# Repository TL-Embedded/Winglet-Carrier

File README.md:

# Winglet Carrier

This is a development board to faciliate testing of the [winglet modems](./winglet-modem.md).

This provides power and connectivity to the modem, and access to all interfaces.

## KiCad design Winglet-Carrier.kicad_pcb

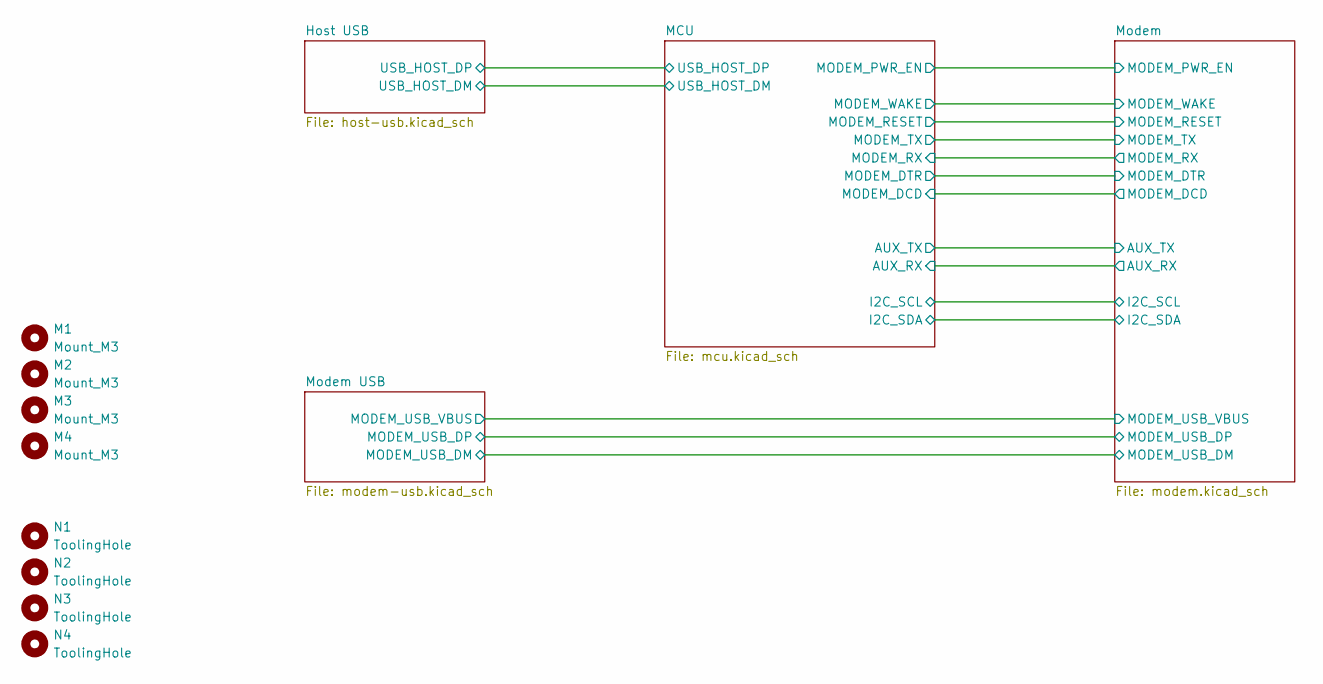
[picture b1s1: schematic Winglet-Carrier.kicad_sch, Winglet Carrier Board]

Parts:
M1, M2, M3, M4: Mount_M3
N1, N2, N3, N4: ToolingHole; ToolingHole_1mm

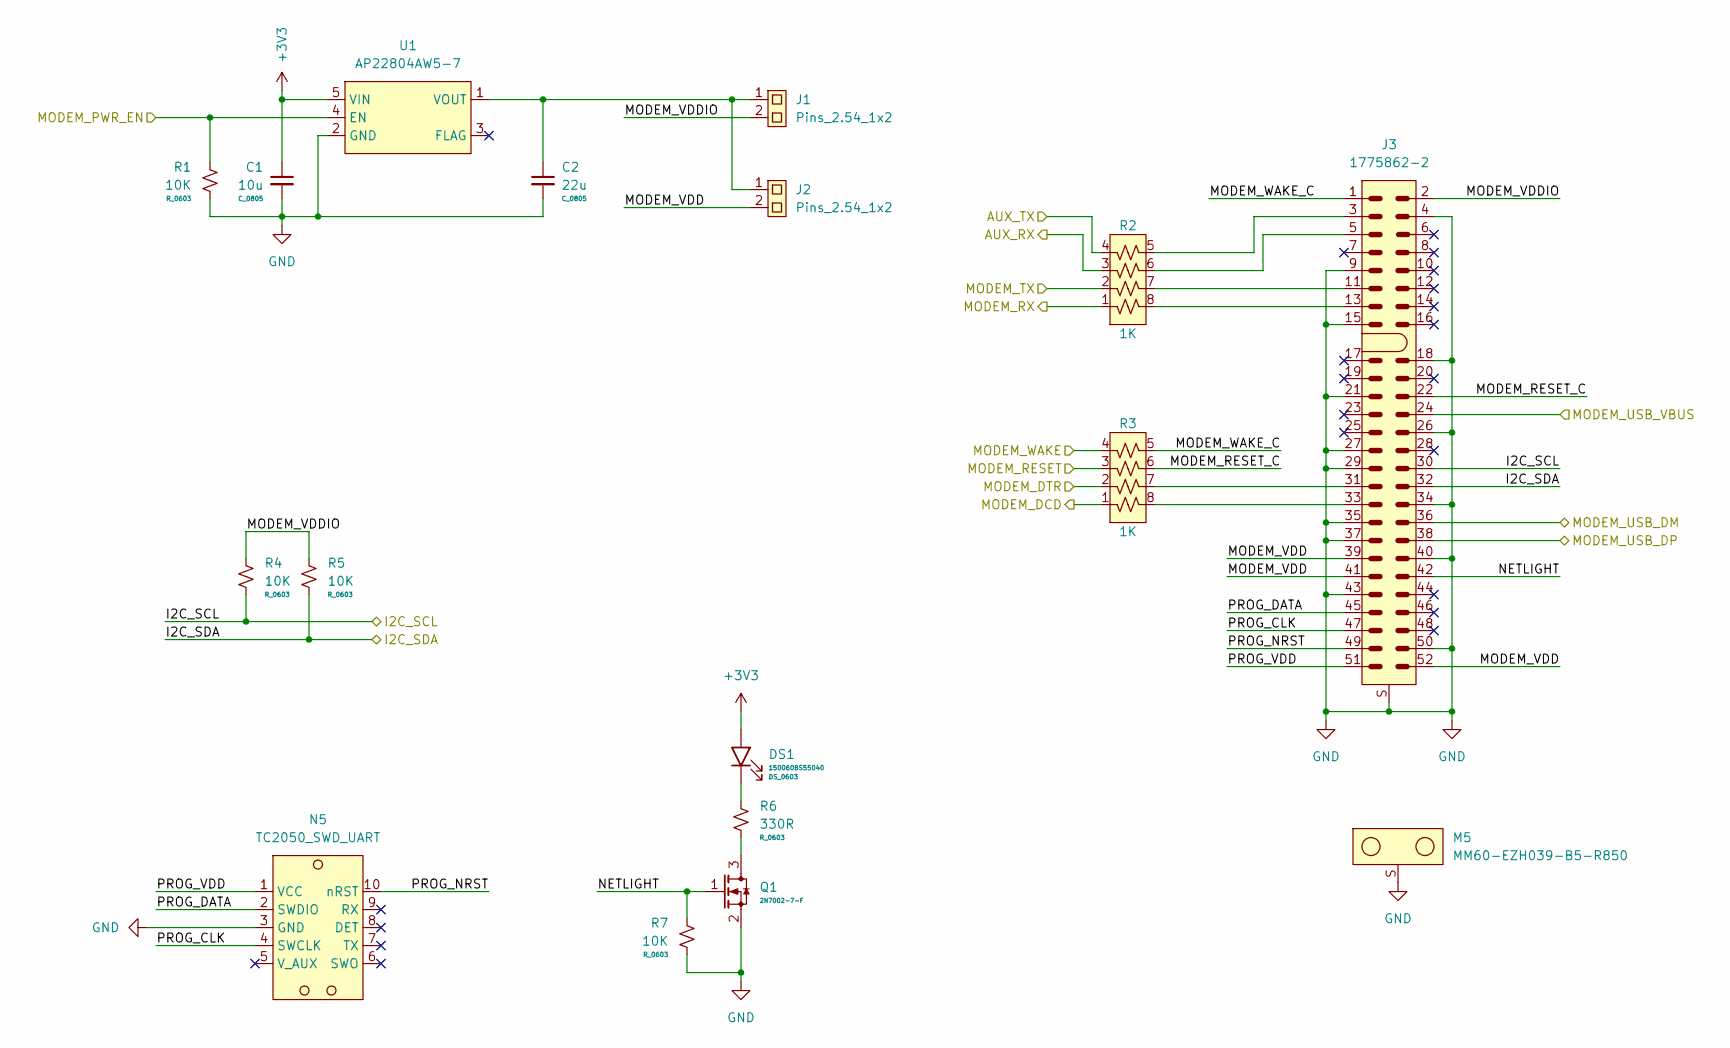
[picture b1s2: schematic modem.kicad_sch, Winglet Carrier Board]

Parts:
C1: 10u; C_0805
C2: 22u; C_0805
DS1: 150060BS55040; DS_0603
J1, J2: Pins_2.54_1x2; Pins-2.54-1x2
J3: 1775862-2
M5: MM60-EZH039-B5-R850
N5: TC2050_SWD_UART; TagConnect_TC2050
Q1: 2N7002-7-F; SOT23_3
R1, R4, R5, R7: 10K; R_0603
R2, R3: 1K; R_Array_1206
R6: 330R; R_0603
U1: AP22804AW5-7; SOT23_5

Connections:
+3V3: C1.1, DS1.2 (A), U1.5 (VIN); also elsewhere on the board
/MCU/AUX_RX: R2.3; also elsewhere on the board
/MCU/AUX_TX: R2.4; also elsewhere on the board
/MCU/MODEM_DCD: R3.1; also elsewhere on the board
/MCU/MODEM_DTR: R3.2; also elsewhere on the board
/MCU/MODEM_PWR_EN: R1.1, U1.4 (EN); also elsewhere on the board
/MCU/MODEM_RESET: R3.3; also elsewhere on the board
/MCU/MODEM_RX: R2.1; also elsewhere on the board
/MCU/MODEM_TX: R2.2; also elsewhere on the board
/MCU/MODEM_WAKE: R3.4; also elsewhere on the board
/Modem USB/MODEM_USB_DM: J3.36; also elsewhere on the board
/Modem USB/MODEM_USB_DP: J3.38; also elsewhere on the board
/Modem USB/MODEM_USB_VBUS: J3.24; also elsewhere on the board
/Modem/I2C_SCL: J3.30, R4.2; also elsewhere on the board
/Modem/I2C_SDA: J3.32, R5.2; also elsewhere on the board
/Modem/MODEM_RESET_C: J3.22, R3.6
/Modem/MODEM_VDD: J2.2, J3.39, J3.41, J3.52
/Modem/MODEM_VDDIO: J1.2, J3.2, R4.1, R5.1
/Modem/MODEM_WAKE_C: J3.1, R3.5
/Modem/NETLIGHT: J3.42, Q1.1 (G), R7.1
/Modem/PROG_CLK: J3.47, N5.4 (SWCLK)
/Modem/PROG_DATA: J3.45, N5.2 (SWDIO)
/Modem/PROG_NRST: J3.49, N5.10 (nRST)
/Modem/PROG_VDD: J3.51, N5.1 (VCC)
GND: C1.2, C2.2, J3.4, J3.9, J3.15, J3.18, J3.21, J3.26, J3.27, J3.29, J3.34, J3.35, J3.37, J3.40, J3.43, J3.50, J3.S, M5.S, N5.3 (GND), Q1.2 (S), R1.2, R7.2, U1.2 (GND); also elsewhere on the board
unnamed: DS1.1 (K), R6.1
unnamed: J3.3, R2.5
unnamed: J3.5, R2.6
unnamed: J3.11, R2.7
unnamed: J3.13, R2.8
unnamed: J3.31, R3.7
unnamed: J3.33, R3.8
unnamed: Q1.3 (D), R6.2
unnamed: C2.1, J1.1, J2.1, U1.1 (VOUT)

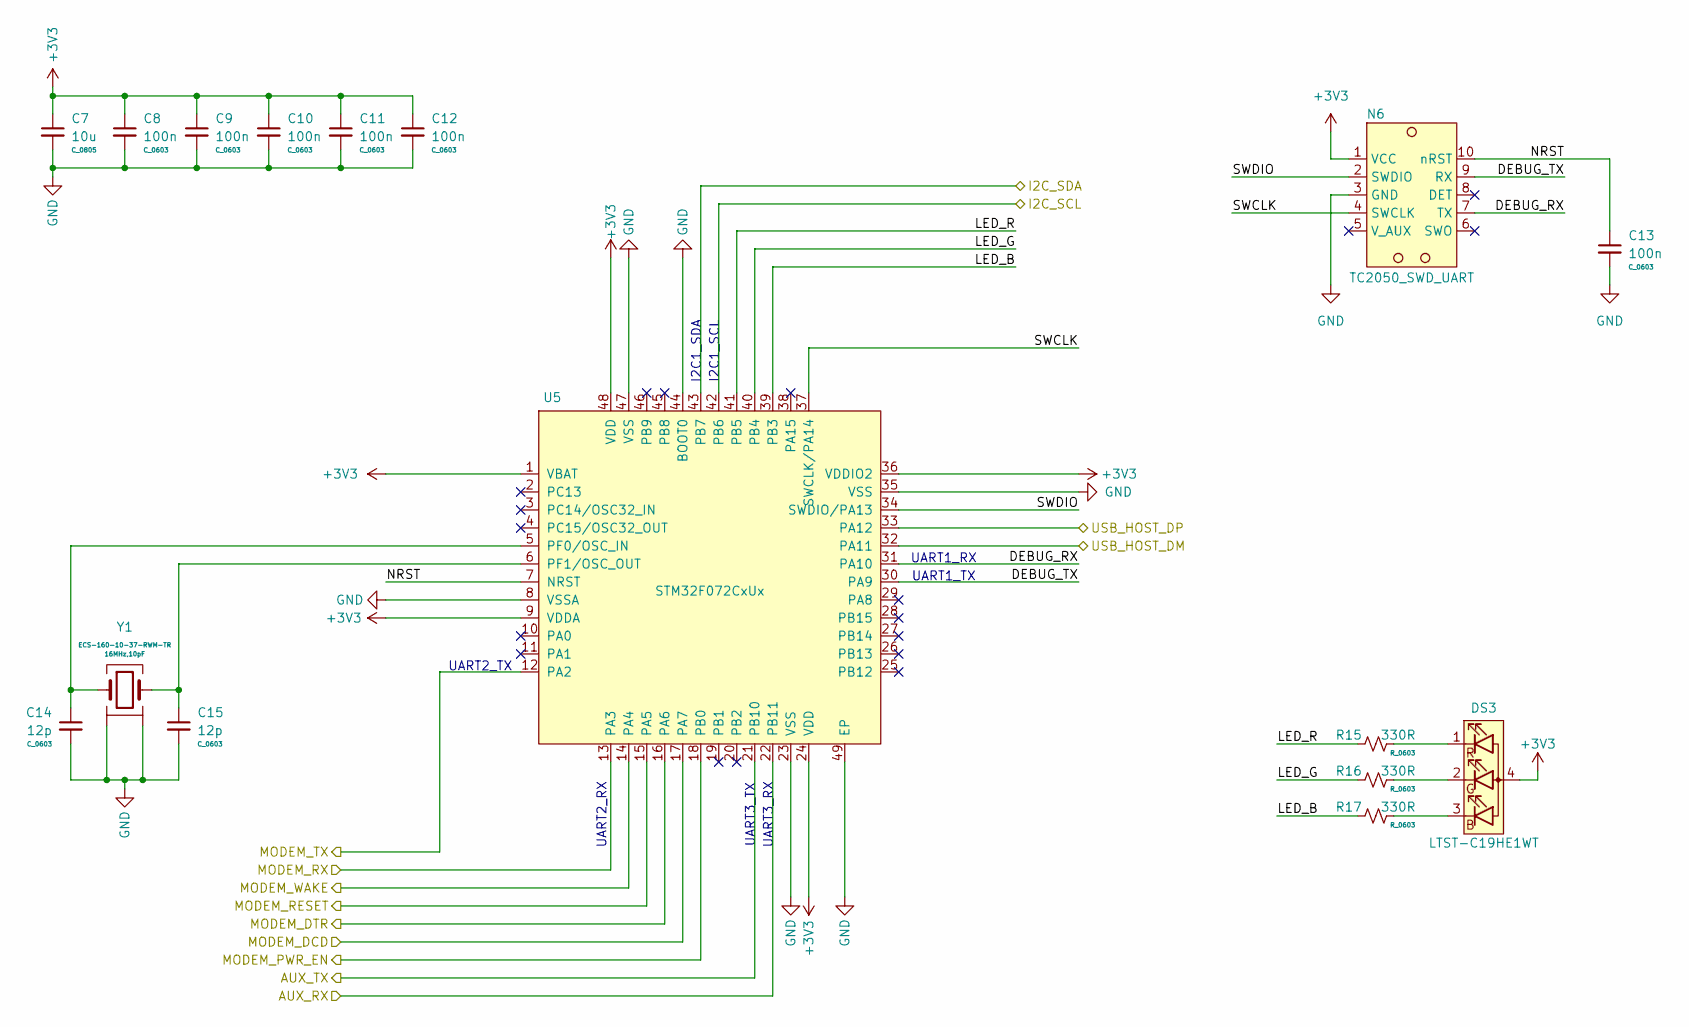
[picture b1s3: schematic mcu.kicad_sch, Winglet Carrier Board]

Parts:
C7: 10u; C_0805
C8, C9, C10, C11, C12, C13: 100n; C_0603
C14, C15: 12p; C_0603
DS3: LTST-C19HE1WT; DS_0606
N6: TC2050_SWD_UART; TagConnect_TC2050
R15, R16, R17: 330R; R_0603
U5: STM32F072CxUx; QFN48_05_7x7_EP
Y1: ECS-160-10-37-RWM-TR; Crystal_SMD4_2.0x1.6

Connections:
+3V3: C7.1, C8.1, C9.1, C10.1, C11.1, C12.1, DS3.4 (A), N6.1 (VCC), U5.1 (VBAT), U5.9 (VDDA), U5.24 (VDD), U5.36 (VDDIO2), U5.48 (VDD); also elsewhere on the board
/Host USB/USB_HOST_DM: U5.32 (PA11); also elsewhere on the board
/Host USB/USB_HOST_DP: U5.33 (PA12); also elsewhere on the board
/MCU/AUX_RX: U5.22 (PB11); also elsewhere on the board
/MCU/AUX_TX: U5.21 (PB10); also elsewhere on the board
/MCU/DEBUG_RX: N6.7 (TX), U5.31 (PA10)
/MCU/DEBUG_TX: N6.9 (RX), U5.30 (PA9)
/MCU/LED_B: R17.1, U5.39 (PB3)
/MCU/LED_G: R16.1, U5.40 (PB4)
/MCU/LED_R: R15.1, U5.41 (PB5)
/MCU/MODEM_DCD: U5.17 (PA7); also elsewhere on the board
/MCU/MODEM_DTR: U5.16 (PA6); also elsewhere on the board
/MCU/MODEM_PWR_EN: U5.18 (PB0); also elsewhere on the board
/MCU/MODEM_RESET: U5.15 (PA5); also elsewhere on the board
/MCU/MODEM_RX: U5.13 (PA3); also elsewhere on the board
/MCU/MODEM_TX: U5.12 (PA2); also elsewhere on the board
/MCU/MODEM_WAKE: U5.14 (PA4); also elsewhere on the board
/MCU/NRST: C13.1, N6.10 (nRST), U5.7 (NRST)
/MCU/SWCLK: N6.4 (SWCLK), U5.37 (SWCLK/PA14)
/MCU/SWDIO: N6.2 (SWDIO), U5.34 (SWDIO/PA13)
/Modem/I2C_SCL: U5.42 (PB6); also elsewhere on the board
/Modem/I2C_SDA: U5.43 (PB7); also elsewhere on the board
GND: C7.2, C8.2, C9.2, C10.2, C11.2, C12.2, C13.2, C14.2, C15.2, N6.3 (GND), U5.8 (VSSA), U5.23 (VSS), U5.35 (VSS), U5.44 (BOOT0), U5.47 (VSS), U5.49 (EP), Y1.2, Y1.4; also elsewhere on the board
unnamed: DS3.3 (BK), R17.2
unnamed: DS3.2 (GK), R16.2
unnamed: DS3.1 (RK), R15.2
unnamed: C14.1, U5.5 (PF0/OSC_IN), Y1.1
unnamed: C15.1, U5.6 (PF1/OSC_OUT), Y1.3

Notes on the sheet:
I2C1_SCL
UART2_RX
UART1_RX
UART3_TX
UART2_TX
UART1_TX
I2C1_SDA
UART3_RX

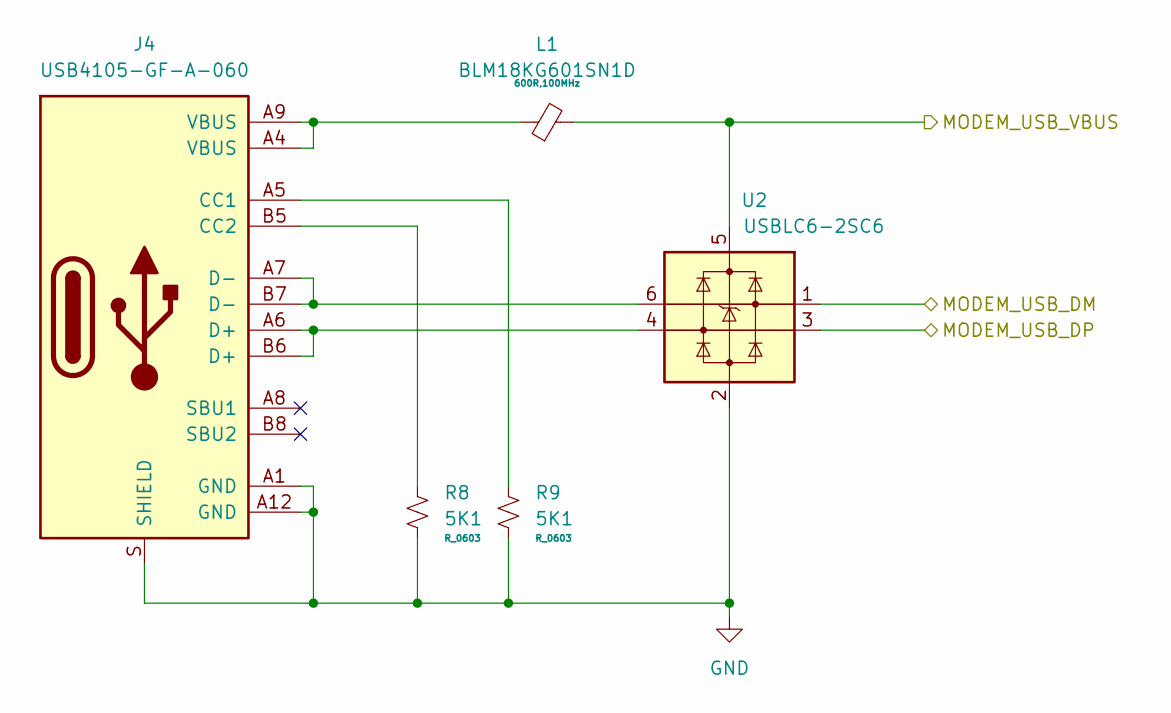
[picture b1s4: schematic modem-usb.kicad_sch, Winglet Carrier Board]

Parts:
J4: USB4105-GF-A-060; USB_C_USB4105-GF-A-060
L1: BLM18KG601SN1D; FB_0603
R8, R9: 5K1; R_0603
U2: USBLC6-2SC6; SOT23_6

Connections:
/Modem USB/MODEM_USB_DM: U2.1; also elsewhere on the board
/Modem USB/MODEM_USB_DP: U2.3; also elsewhere on the board
/Modem USB/MODEM_USB_VBUS: L1.2, U2.5; also elsewhere on the board
GND: J4.A1 (GND), J4.A12 (GND), J4.S (SHIELD), R8.2, R9.2, U2.2; also elsewhere on the board
unnamed: J4.A5 (CC1), R9.1
unnamed: J4.B5 (CC2), R8.1
unnamed: J4.A6 (D+), J4.B6 (D+), U2.4
unnamed: J4.A7 (D-), J4.B7 (D-), U2.6
unnamed: J4.A4 (VBUS), J4.A9 (VBUS), L1.1

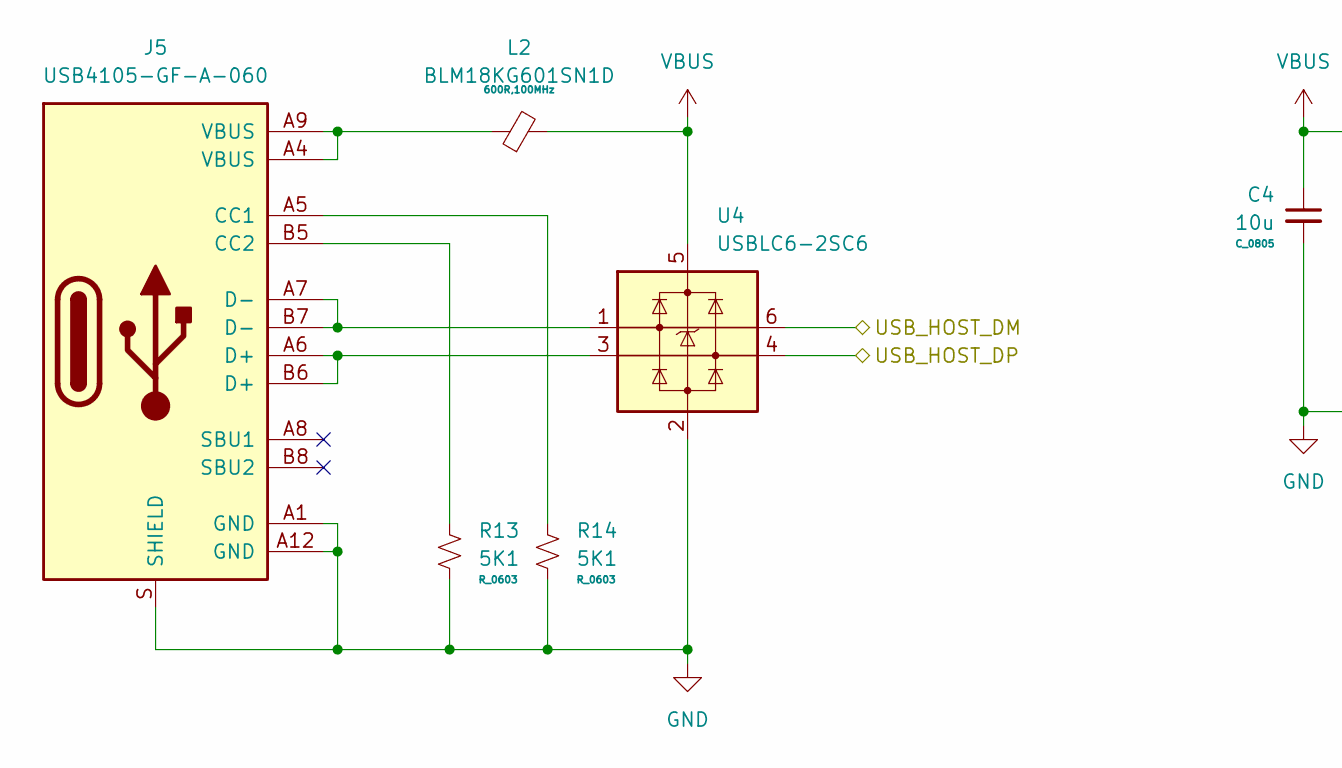
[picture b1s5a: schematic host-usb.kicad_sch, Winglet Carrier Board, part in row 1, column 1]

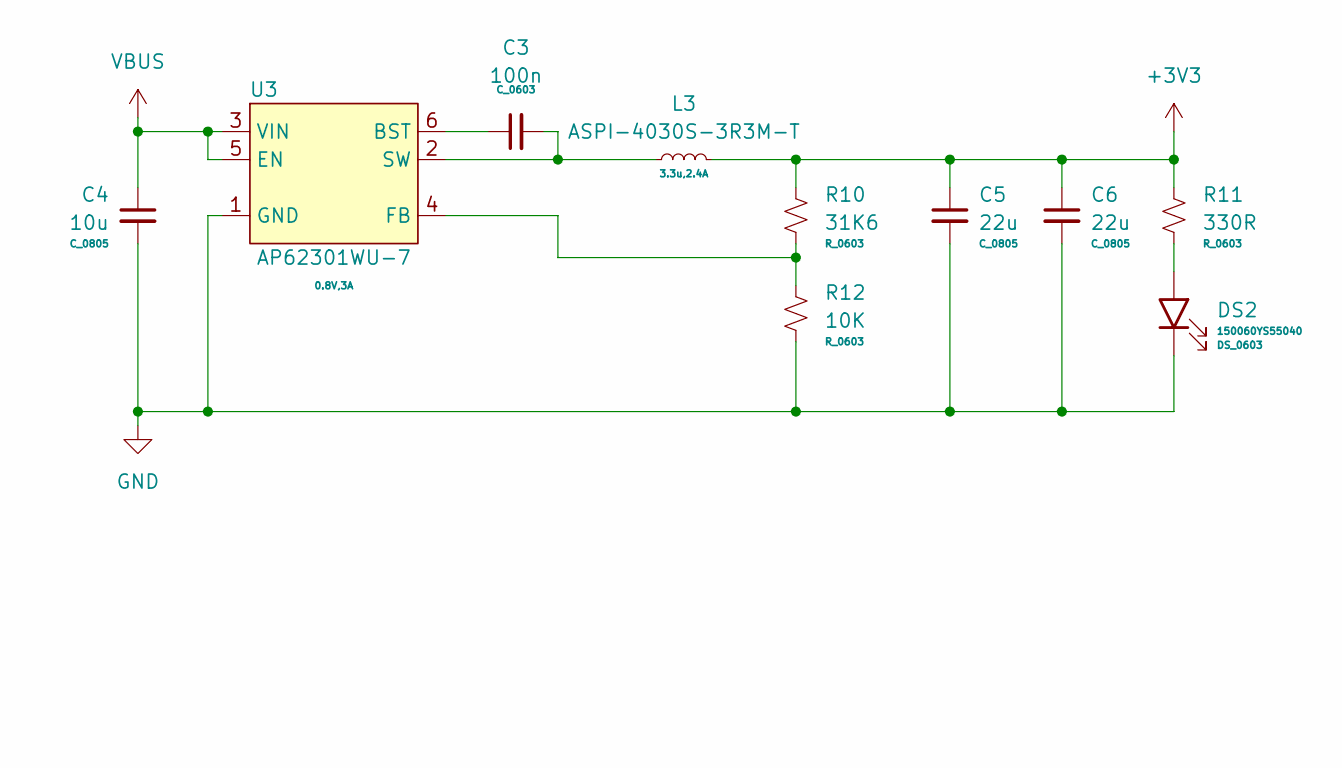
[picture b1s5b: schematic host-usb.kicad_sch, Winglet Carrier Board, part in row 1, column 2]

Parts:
C3: 100n; C_0603
C4: 10u; C_0805
C5, C6: 22u; C_0805
DS2: 150060YS55040; DS_0603
J5: USB4105-GF-A-060; USB_C_USB4105-GF-A-060
L2: BLM18KG601SN1D; FB_0603
L3: ASPI-4030S-3R3M-T; L_4030S
R10: 31K6; R_0603
R11: 330R; R_0603
R12: 10K; R_0603
R13, R14: 5K1; R_0603
U3: AP62301WU-7; SOT23_6
U4: USBLC6-2SC6; SOT23_6

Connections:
+3V3: C5.1, C6.1, L3.2, R10.1, R11.1; also elsewhere on the board
/Host USB/USB_HOST_DM: U4.6; also elsewhere on the board
/Host USB/USB_HOST_DP: U4.4; also elsewhere on the board
GND: C4.2, C5.2, C6.2, DS2.1 (K), J5.A1 (GND), J5.A12 (GND), J5.S (SHIELD), R12.2, R13.2, R14.2, U3.1 (GND), U4.2; also elsewhere on the board
unnamed: DS2.2 (A), R11.2
unnamed: J5.A5 (CC1), R14.1
unnamed: J5.B5 (CC2), R13.1
unnamed: J5.A6 (D+), J5.B6 (D+), U4.3
unnamed: J5.A7 (D-), J5.B7 (D-), U4.1
unnamed: J5.A4 (VBUS), J5.A9 (VBUS), L2.1
unnamed: C3.1, U3.6 (BST)
unnamed: R10.2, R12.1, U3.4 (FB)
unnamed: C3.2, L3.1, U3.2 (SW)
VBUS: C4.1, L2.2, U3.3 (VIN), U3.5 (EN), U4.5

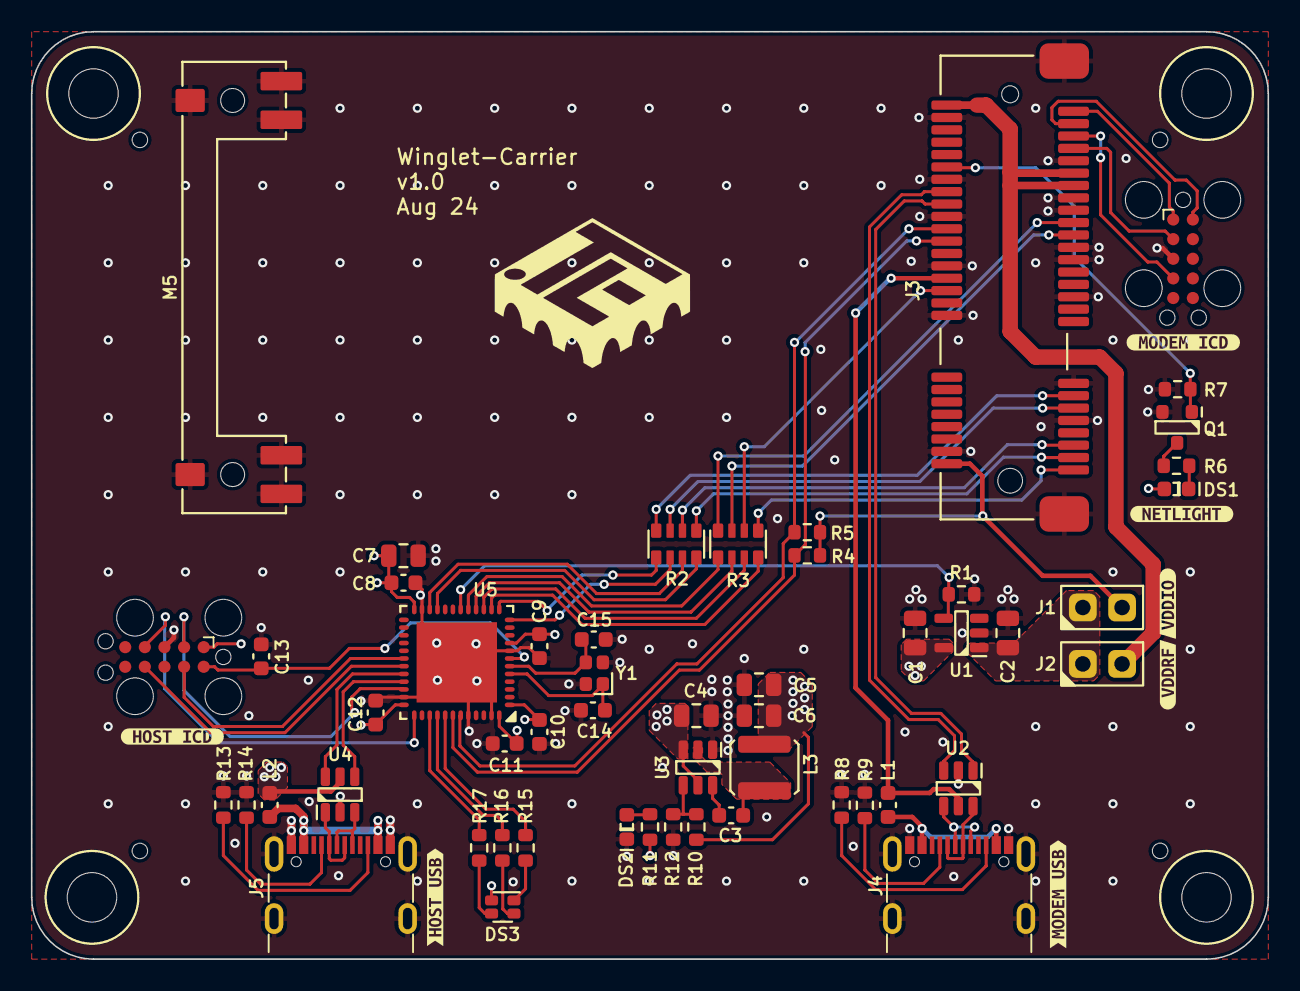
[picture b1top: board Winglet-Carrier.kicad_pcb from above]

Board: 4 copper layers, 80.0 x 60.0 mm, 68 parts (0 on the bottom side), 64 nets.

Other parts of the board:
kibuzzard-66B59BD0: G***; kibuzzard-66B59BD0
kibuzzard-66B59C2B: G***; kibuzzard-66B59C2B
kibuzzard-66B59C6F: G***; kibuzzard-66B59C6F
kibuzzard-66B59C7E: G***; kibuzzard-66B59C7E
kibuzzard-66B59C9C: G***; kibuzzard-66B59C9C
kibuzzard-66B59C37: G***; kibuzzard-66B59C37
kibuzzard-66B59CA2: G***; kibuzzard-66B59CA2

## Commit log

2024-08-09 Initial design
2024-08-09 Reannotate components
2024-08-09 Add output generation
2024-08-09 Add some docs
